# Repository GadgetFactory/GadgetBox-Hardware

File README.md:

GadgetBox tackles the biggest problems with current IoT devices – shield stacking, easily adding hardware, hardware compatibility, and an enclosure for your project. There are lots of IoT hardware options out there but none of them have thought the problem all the way through, so what we end up with is either a crazy tower of shields or peripherals soldered on with jumper wires. Not something we can proudly show our friends and family, let alone put into use in our homes.

GadgetBox starts with a case and builds from there – so the end result is an attractive, functional device with all of the electronics safely contained in the case.

Inside the GadgetBox case is a motherboard that provides all of the circuitry to charge and use a Lipo battery pack, provide higher current to your peripherals, and organizes all IO pins into the Universal eCog scheme. A motherboard for all of the most popular IoT devices is currently in the works – Arduino, Teensy, Pi Zero, ESP8266, etc.

eCogs are Universal peripherals that just snap into the motherboard and form the top of your enclosure. Only the hardware that is needed by the end user is exposed to the outside world, everything else is tucked inside the enclosure. Because the motherboards are designed using the Universal eCog scheme you can freely interchange your eCogs between motherboards. If you have an SD card eCog shouldn’t you be able to use that same eCog with the Arduino, Teensy, Pi Zero, and ESP8266? Of course you should, the Universal eCog scheme makes that possible.

Learn more at:
https://hackaday.io/project/12426-gadgetbox-no-more-shield-stacking-or-ugly-wires
http://GadgetBox.GadgetFactory.net

# GadgetBox-Hardware

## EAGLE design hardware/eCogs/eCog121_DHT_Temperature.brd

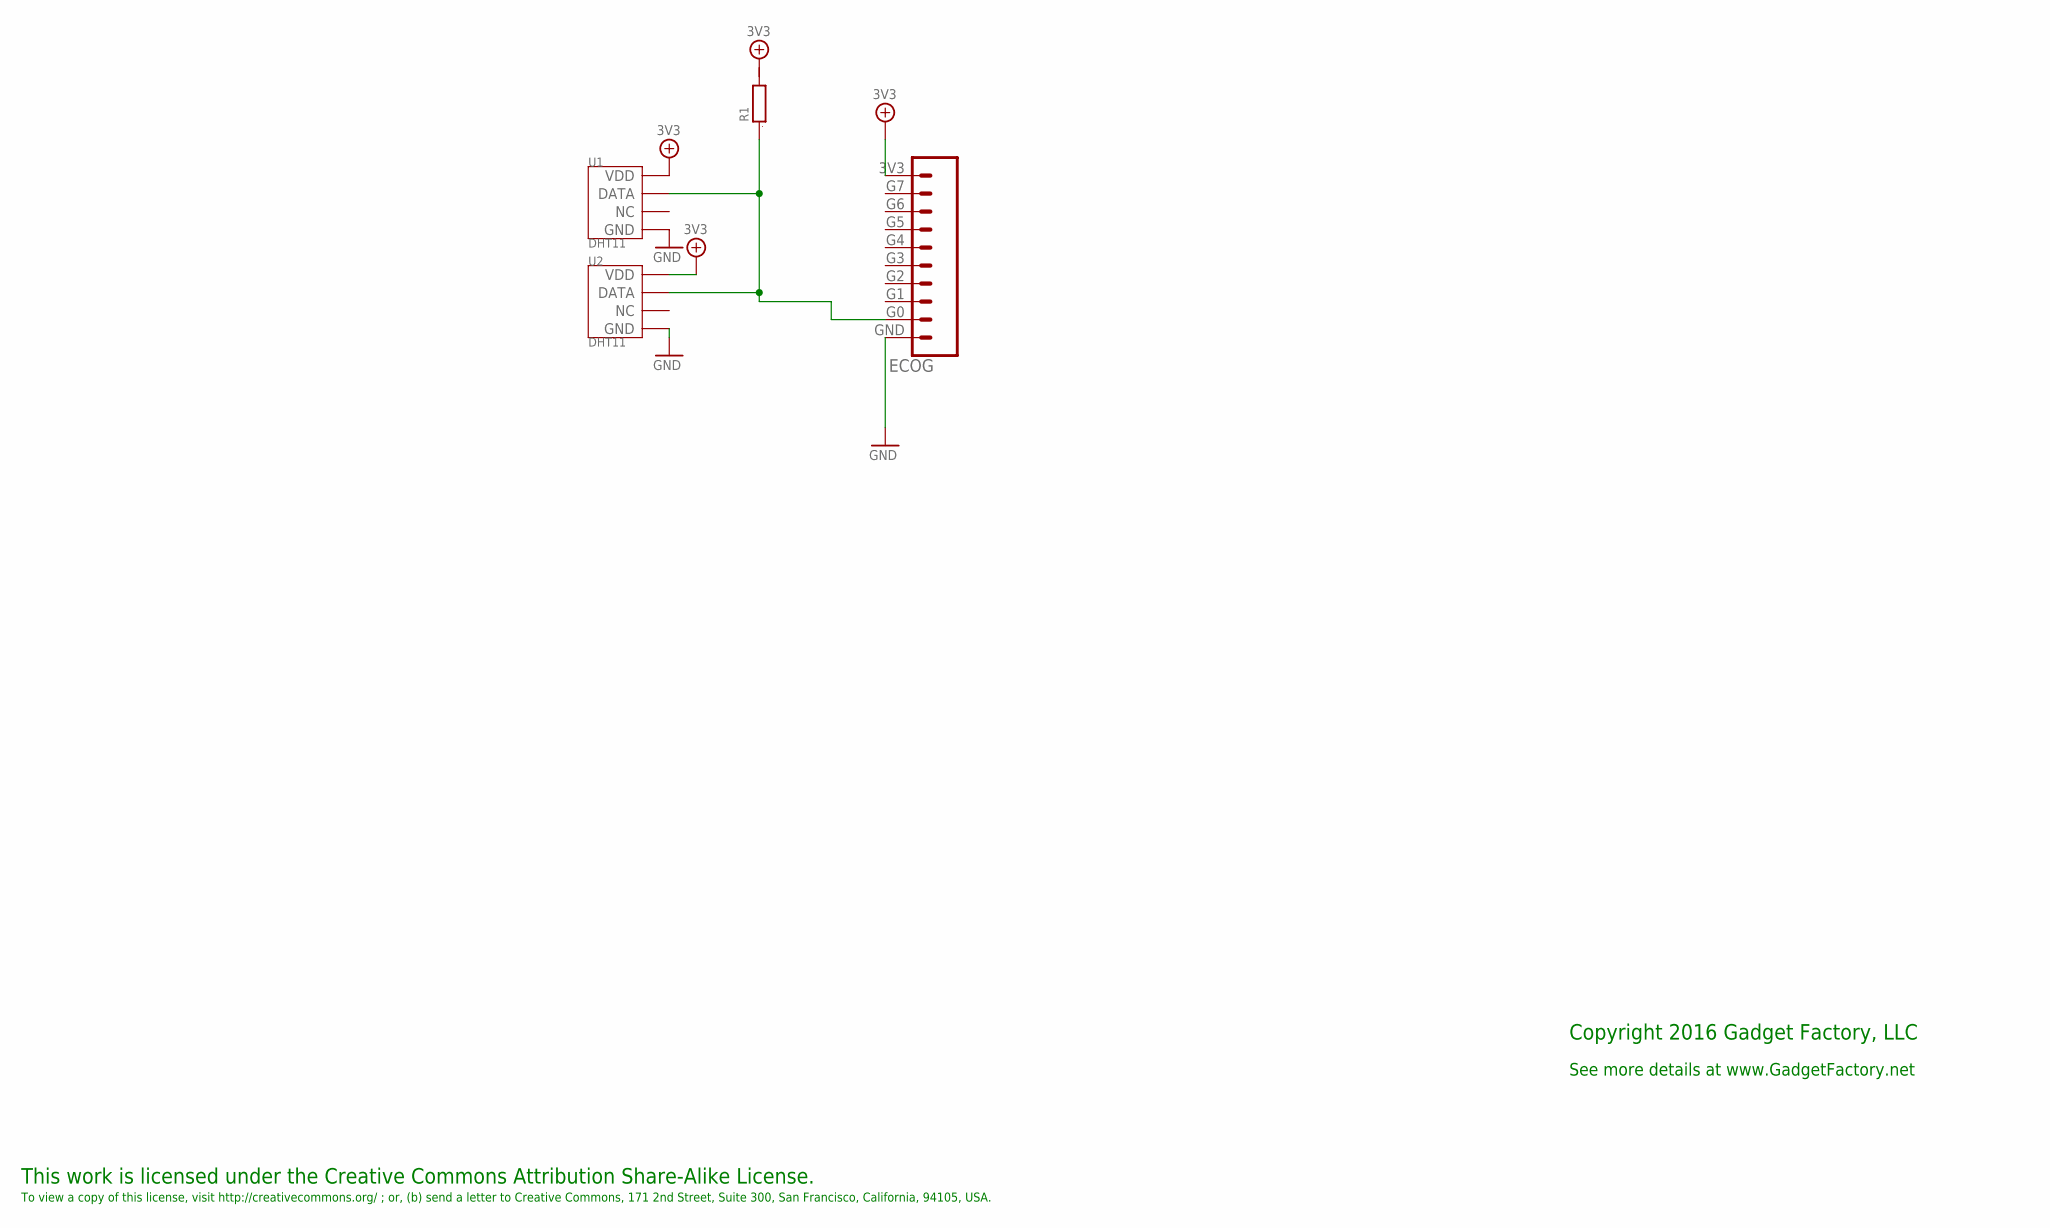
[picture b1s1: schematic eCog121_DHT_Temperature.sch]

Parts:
ECOG: ECOG_GENERAL_ROWTHROUGHOLE; ECOG_GENERAL_TH
R1: R0805; 0805
U1, U2: DHT11; SNR4-2.54-15.5X12.0X5.5MM

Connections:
3V3: ECOG.3V3, U1.1 (VDD)
GND: ECOG.GND, U1.4 (GND), U2.4 (GND)
unnamed: ECOG.G0, R1.1, U1.2 (DATA), U2.2 (DATA)
VDD: U2.1 (VDD)

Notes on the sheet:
This work is licensed under the Creative Commons Attribution Share-Alike License.
To view a copy of this license, visit http://creativecommons.org/ ; or, (b) send a letter to Creative Commons, 171 2nd Street, Suite 300, San Francisco, California, 94105, USA.
Copyright 2016 Gadget Factory, LLC
See more details at www.GadgetFactory.net

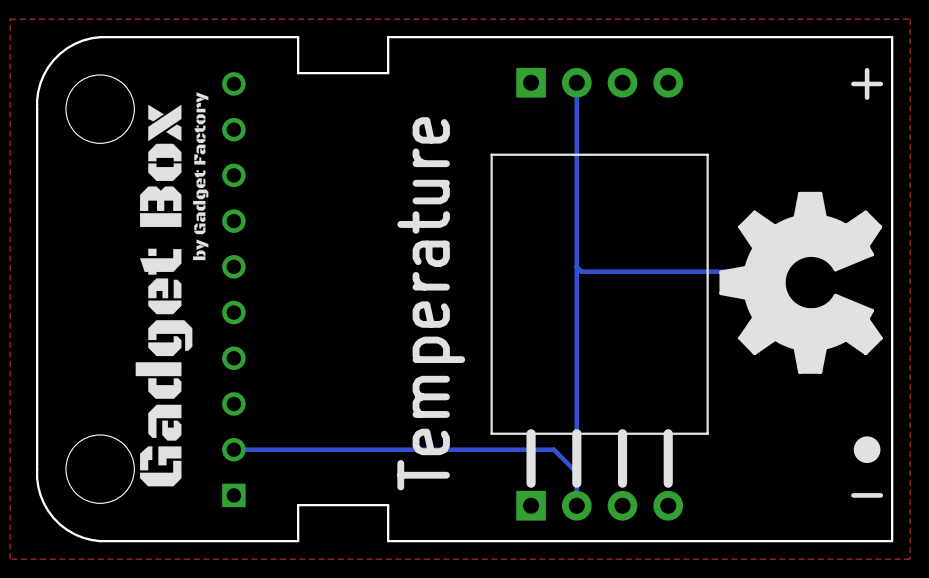
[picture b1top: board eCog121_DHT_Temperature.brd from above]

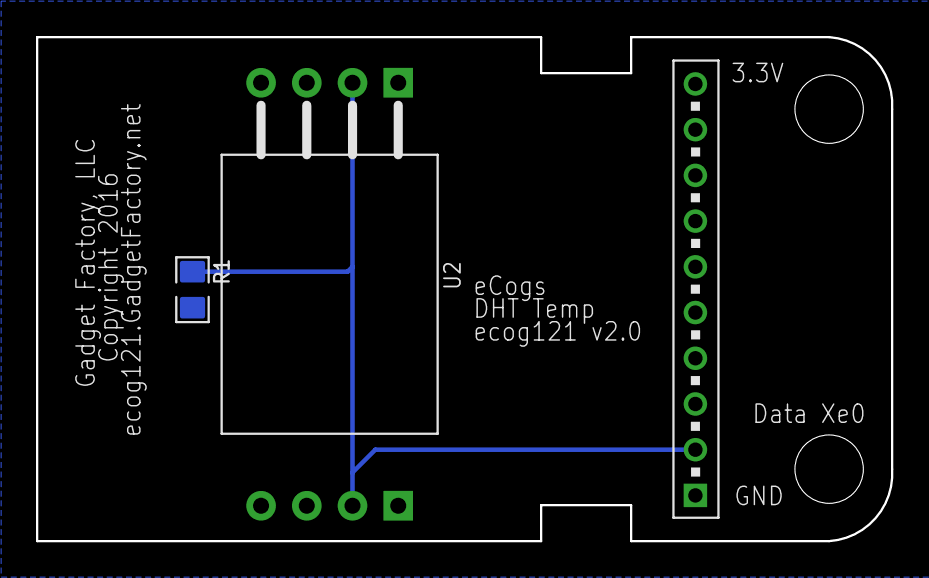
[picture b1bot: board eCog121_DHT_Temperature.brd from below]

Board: 2 copper layers, 47.5 x 28.0 mm, 7 parts (2 on the bottom side), 3 nets.

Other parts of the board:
U$1: GADGETBOX_SMALL
U$2: LEGEND_DIO
U$10: OSHW_FILLX350_NOTEXT

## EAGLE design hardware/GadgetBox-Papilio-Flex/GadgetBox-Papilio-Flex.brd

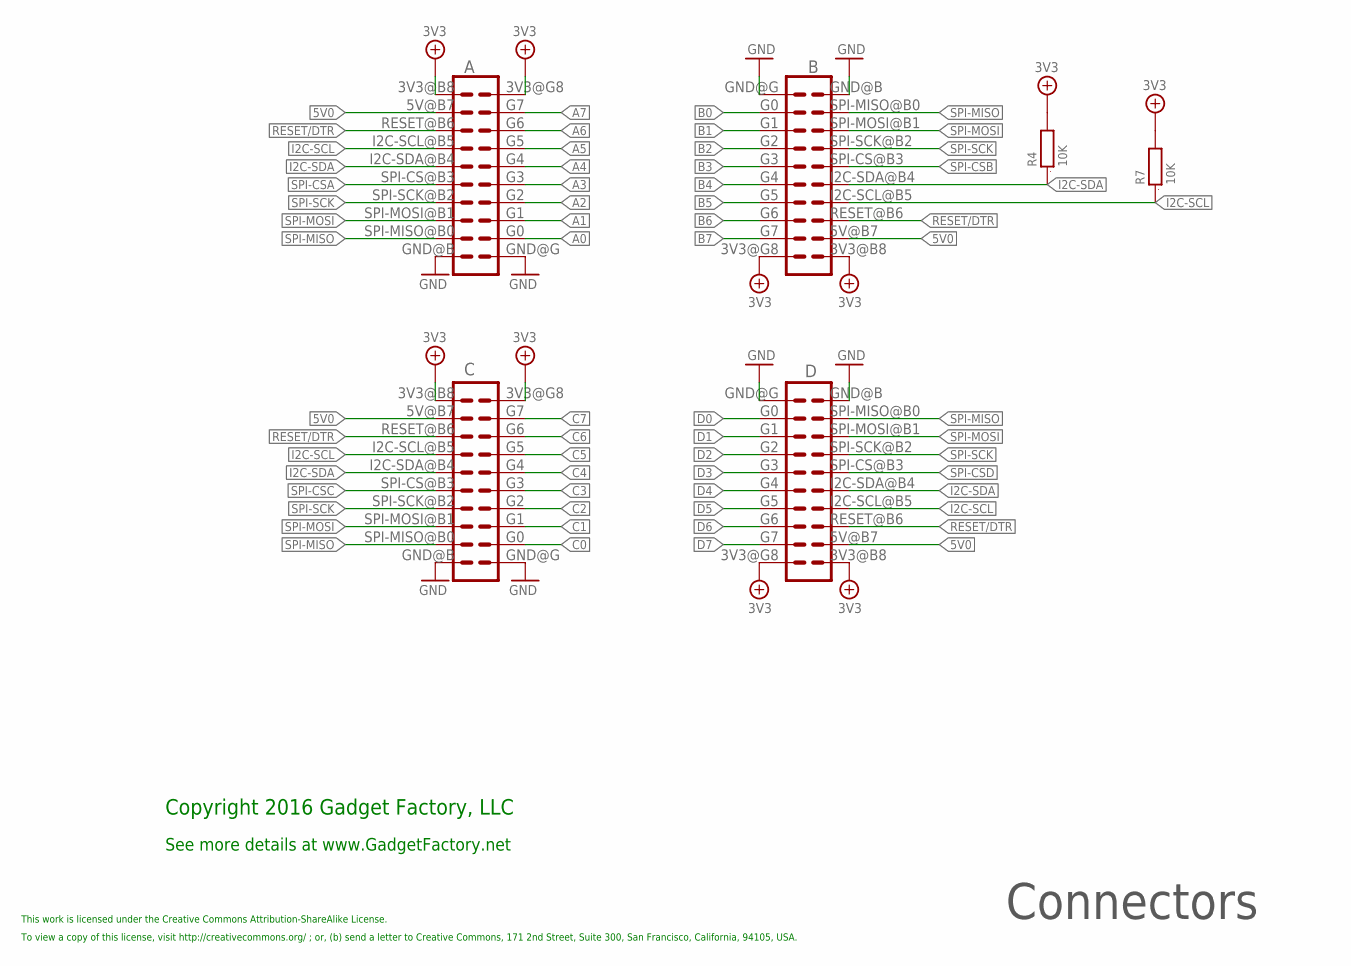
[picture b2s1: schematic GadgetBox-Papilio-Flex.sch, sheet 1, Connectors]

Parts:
A: ECOGECOG_SLOT_ALT1; ECOG_ALT1; PARTNO PPPC102LFBN-RC,SULLINS CONNECTOR SOLUTI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
B: ECOGECOG_SLOT_ALT1; ECOG_ALT1; PARTNO PPPC102LFBN-RC,SULLINS CONNECTOR SOLUTI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
C: ECOGECOG_SLOT_ALT1; ECOG_ALT1; PARTNO PPPC102LFBN-RC,SULLINS CONNECTOR SOLUTI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
D: ECOGECOG_SLOT_ALT1; ECOG_ALT1; PARTNO PPPC102LFBN-RC,SULLINS CONNECTOR SOLUTI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
R4, R7: 10K; 0603; PARTNO RC0603JR-0710KL,YAGEO (VA),dk,311-10KGR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

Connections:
3V3: A.3V3@B8 (3V3), A.3V3@G8 (3V3), B.3V3@B8 (3V3), B.3V3@G8 (3V3), C.3V3@B8 (3V3), C.3V3@G8 (3V3), D.3V3@B8 (3V3), D.3V3@G8 (3V3), R4.2, R7.2; also elsewhere on the board
5V0: A.5V@B7 (5V), B.5V@B7 (5V), C.5V@B7 (5V), D.5V@B7 (5V); also elsewhere on the board
A0: A.G0; also elsewhere on the board
A1: A.G1; also elsewhere on the board
A2: A.G2; also elsewhere on the board
A3: A.G3; also elsewhere on the board
A4: A.G4; also elsewhere on the board
A5: A.G5; also elsewhere on the board
A6: A.G6; also elsewhere on the board
A7: A.G7; also elsewhere on the board
B0: B.G0; also elsewhere on the board
B1: B.G1; also elsewhere on the board
B2: B.G2; also elsewhere on the board
B3: B.G3; also elsewhere on the board
B4: B.G4; also elsewhere on the board
B5: B.G5; also elsewhere on the board
B6: B.G6; also elsewhere on the board
B7: B.G7; also elsewhere on the board
C0: C.G0; also elsewhere on the board
C1: C.G1; also elsewhere on the board
C2: C.G2; also elsewhere on the board
C3: C.G3; also elsewhere on the board
C4: C.G4; also elsewhere on the board
C5: C.G5; also elsewhere on the board
C6: C.G6; also elsewhere on the board
C7: C.G7; also elsewhere on the board
D0: D.G0; also elsewhere on the board
D1: D.G1; also elsewhere on the board
D2: D.G2; also elsewhere on the board
D3: D.G3; also elsewhere on the board
D4: D.G4; also elsewhere on the board
D5: D.G5; also elsewhere on the board
D6: D.G6; also elsewhere on the board
D7: D.G7; also elsewhere on the board
GND: A.GND@B (GND), A.GND@G (GND), B.GND@B (GND), B.GND@G (GND), C.GND@B (GND), C.GND@G (GND), D.GND@B (GND), D.GND@G (GND); also elsewhere on the board
I2C-SCL: A.I2C-SCL@B5 (I2C-SCL), B.I2C-SCL@B5 (I2C-SCL), C.I2C-SCL@B5 (I2C-SCL), D.I2C-SCL@B5 (I2C-SCL), R7.1; also elsewhere on the board
I2C-SDA: A.I2C-SDA@B4 (I2C-SDA), B.I2C-SDA@B4 (I2C-SDA), C.I2C-SDA@B4 (I2C-SDA), D.I2C-SDA@B4 (I2C-SDA), R4.1; also elsewhere on the board
RESET/DTR: A.RESET@B6 (RESET), B.RESET@B6 (RESET), C.RESET@B6 (RESET), D.RESET@B6 (RESET); also elsewhere on the board
SPI-CSA: A.SPI-CS@B3 (SPI-CS); also elsewhere on the board
SPI-CSB: B.SPI-CS@B3 (SPI-CS); also elsewhere on the board
SPI-CSC: C.SPI-CS@B3 (SPI-CS); also elsewhere on the board
SPI-CSD: D.SPI-CS@B3 (SPI-CS); also elsewhere on the board
SPI-MISO: A.SPI-MISO@B0 (SPI-MISO), B.SPI-MISO@B0 (SPI-MISO), C.SPI-MISO@B0 (SPI-MISO), D.SPI-MISO@B0 (SPI-MISO); also elsewhere on the board
SPI-MOSI: A.SPI-MOSI@B1 (SPI-MOSI), B.SPI-MOSI@B1 (SPI-MOSI), C.SPI-MOSI@B1 (SPI-MOSI), D.SPI-MOSI@B1 (SPI-MOSI); also elsewhere on the board
SPI-SCK: A.SPI-SCK@B2 (SPI-SCK), B.SPI-SCK@B2 (SPI-SCK), C.SPI-SCK@B2 (SPI-SCK), D.SPI-SCK@B2 (SPI-SCK); also elsewhere on the board

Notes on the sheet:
Connectors
Copyright 2016 Gadget Factory, LLC
See more details at www.GadgetFactory.net
This work is licensed under the Creative Commons Attribution-ShareAlike License.
To view a copy of this license, visit http://creativecommons.org/ ; or, (b) send a letter to Creative Commons, 171 2nd Street, Suite 300, San Francisco, California, 94105, USA.

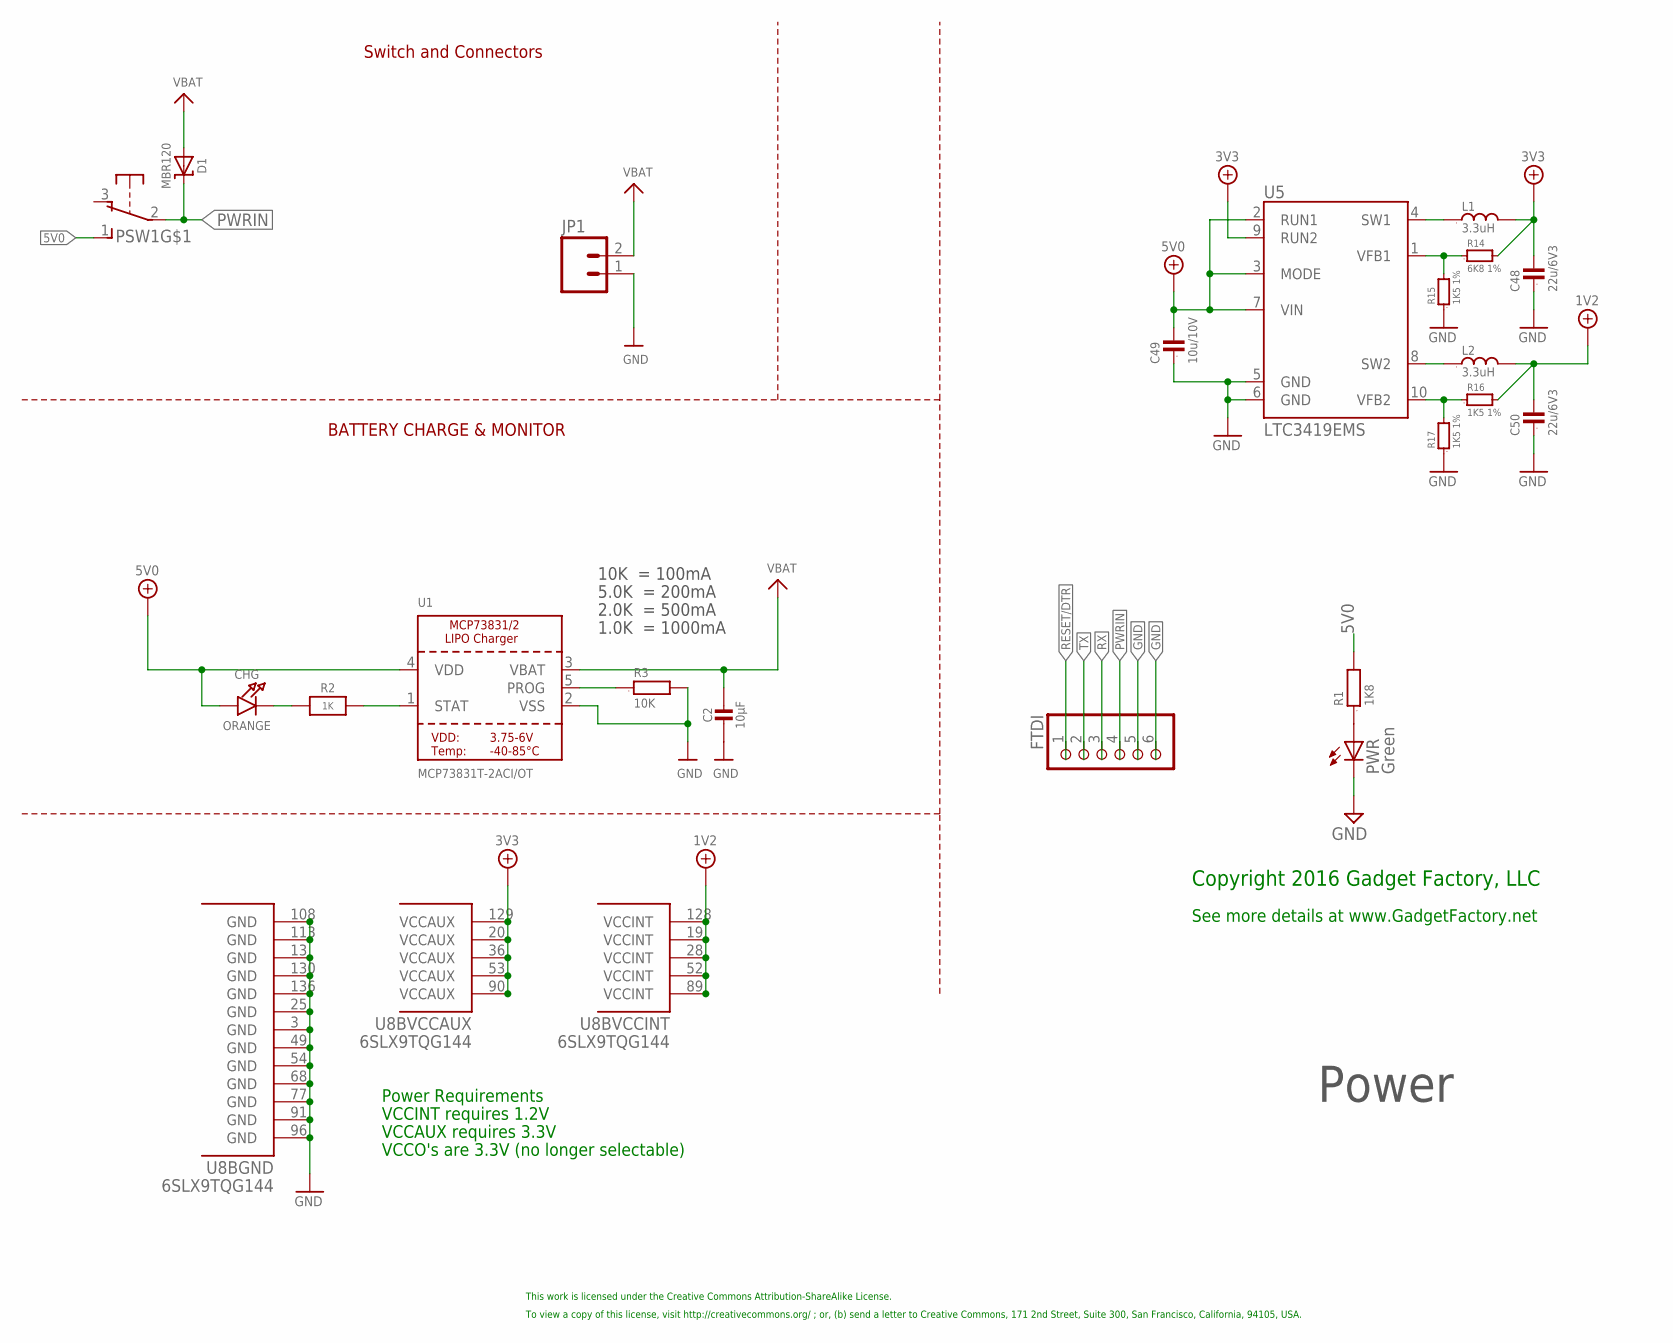
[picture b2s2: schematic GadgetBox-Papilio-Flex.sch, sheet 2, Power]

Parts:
C2: 10µF; 0805-NO; PARTNO CL21F106ZPFNNNE,Samsung,DK,1276-3012-1-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
C48, C50: 22u/6V3; 0805; PARTNO GRM21BR60J226ME39L,MURATA ELECTRONICS (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
C49: 10u/10V; 0805; PARTNO C2012Y5V1A106Z,TDK CORPORATION (VA),DK,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
CHG: ORANGE; CHIPLED_0805_NOOUTLINE; PARTNO LTST-C171EKT,LITE-ON INC (VA),DK,160-14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
D1: MBR120; SOD-123; PARTNO MBR120VLSFT3G,on semiconductor,dk,MBR12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
FTDI: PINHD-1X6; 1X06; PARTNO PPPC061LGBN-RC,SULLINS CONNECTOR SOLUTI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
JP1: M02JST-PTH-2; JST-2-PTH; PARTNO B2B-PH-SM4-TB(LF)(SN),JST SALES AMERICA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
L1, L2: 3.3uH; VLS3015; PARTNO VLS3015T-3R3M1R2,TDK CORPORATION (VA),D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
PSW1: OS102011MA1Q; PARTNO OS102011MA1QN1,C&K Components,dk,CKN955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
PWR: Green; CHIP-LED0805; PARTNO LTST-C170KGKT,LITE-ON INC (VA),DK,160-1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
R1: 1K8; 0805; PARTNO MCR10EZPJ182,ROHM SEMICONDUCTOR (PASSIV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
R2: 1K; 0603-NO; PARTNO RC0603JR-071KL,YAGEO (VA),dk,311-1.0KGR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
R3: 10K; 0603; PARTNO RC0603JR-0710KL,YAGEO (VA),dk,311-10KGR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
R14: 6K8 1%; 0603; PARTNO CRCW06036K80FKEA,VISHAY DALE (VA),DK,54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
R15, R16, R17: 1K5 1%; 0603; PARTNO CRCW06031K50FKEA,VISHAY DALE (VA),DK,54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
U1: MCP73831T-2ACI/OT; SOT23-5; PARTNO MCP73831T-2ACI/OT,MICROCHIP TECHNOLOGY 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
U5: LTC3419EMS; MSOP10; PARTNO LTC3419EMS#PBF,LINEAR TECHNOLOGY,DK,LTC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; DIGIKEY LTC3419EMS#PBF-ND
U8: 6SLX9TQG144; TQ144; PARTNO XC6SLX9-2TQG144C,XILINX INC,DK,122-1745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

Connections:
1V2: C50.2, L2.2, R16.2, U8.19 (VCCINT), U8.28 (VCCINT), U8.52 (VCCINT), U8.89 (VCCINT), U8.128 (VCCINT); also elsewhere on the board
3V3: C48.2, L1.2, R14.2, U5.9 (RUN2), U8.20 (VCCAUX), U8.36 (VCCAUX), U8.53 (VCCAUX), U8.90 (VCCAUX), U8.129 (VCCAUX); also elsewhere on the board
5V0: C49.2, CHG.A, PSW1.1 (S), R1.2, U1.4 (VDD), U5.2 (RUN1), U5.3 (MODE), U5.7 (VIN); also elsewhere on the board
FB_1V2: R16.1, R17.2, U5.10 (VFB2)
FB_3V3: R14.1, R15.2, U5.1 (VFB1)
GND: C2.2, C48.1, C49.1, C50.1, FTDI.5, FTDI.6, JP1.1, PWR.C, R3.2, R15.1, R17.1, U1.2 (VSS), U5.5 (GND), U5.6 (GND), U8.3 (GND), U8.13 (GND), U8.25 (GND), U8.49 (GND), U8.54 (GND), U8.68 (GND), U8.77 (GND), U8.91 (GND), U8.96 (GND), U8.108 (GND), U8.113 (GND), U8.130 (GND), U8.136 (GND); also elsewhere on the board
unnamed: PWR.A, R1.1
unnamed: CHG.C, R2.1
unnamed: R2.2, U1.1 (STAT)
unnamed: R3.1, U1.5 (PROG)
PWRIN: D1.C, FTDI.4, PSW1.2; also elsewhere on the board
RESET/DTR: FTDI.1; also elsewhere on the board
RX: FTDI.3; also elsewhere on the board
SW_1V2: L2.1, U5.8 (SW2)
SW_3V3: L1.1, U5.4 (SW1)
TX: FTDI.2; also elsewhere on the board
VBAT: C2.1, D1.A, JP1.2, U1.3 (VBAT)

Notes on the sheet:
Switch and Connectors
BATTERY CHARGE & MONITOR
10K = 100mA
5.0K = 200mA
2.0K = 500mA
1.0K = 1000mA
Power Requirements
VCCINT requires 1.2V
VCCAUX requires 3.3V
VCCO's are 3.3V (no longer selectable)
Power
Copyright 2016 Gadget Factory, LLC
See more details at www.GadgetFactory.net
This work is licensed under the Creative Commons Attribution-ShareAlike License.
To view a copy of this license, visit http://creativecommons.org/ ; or, (b) send a letter to Creative Commons, 171 2nd Street, Suite 300, San Francisco, California, 94105, USA.

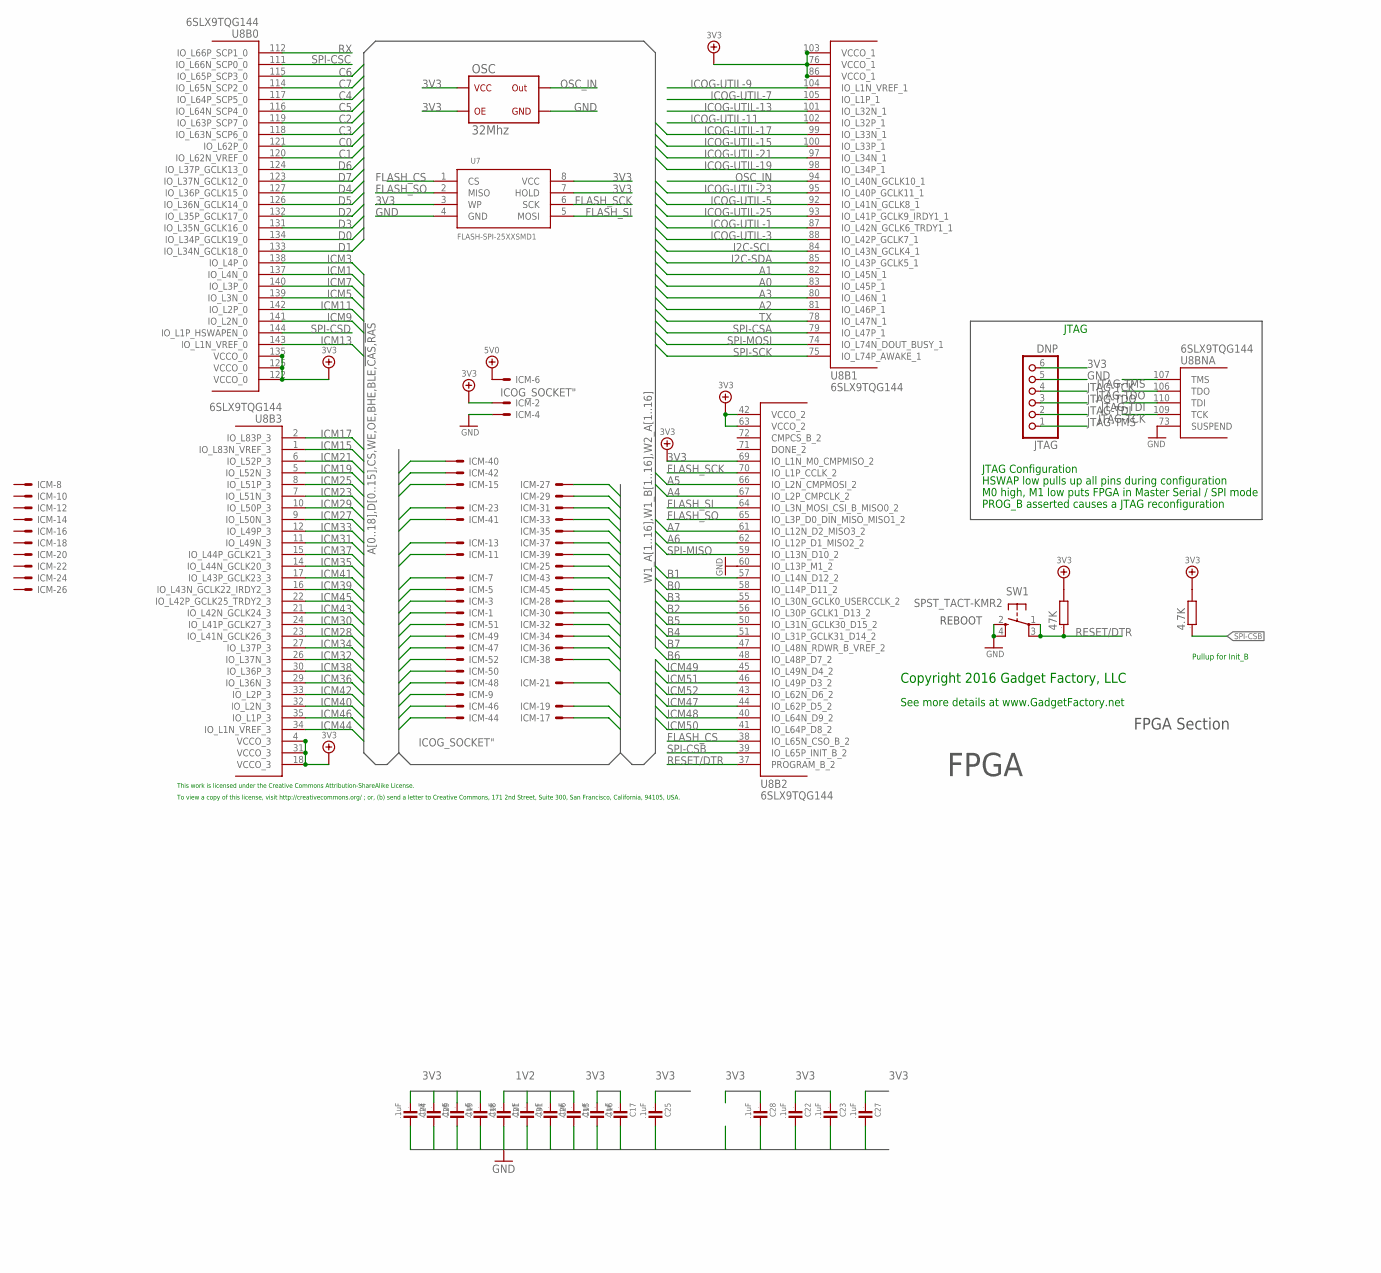
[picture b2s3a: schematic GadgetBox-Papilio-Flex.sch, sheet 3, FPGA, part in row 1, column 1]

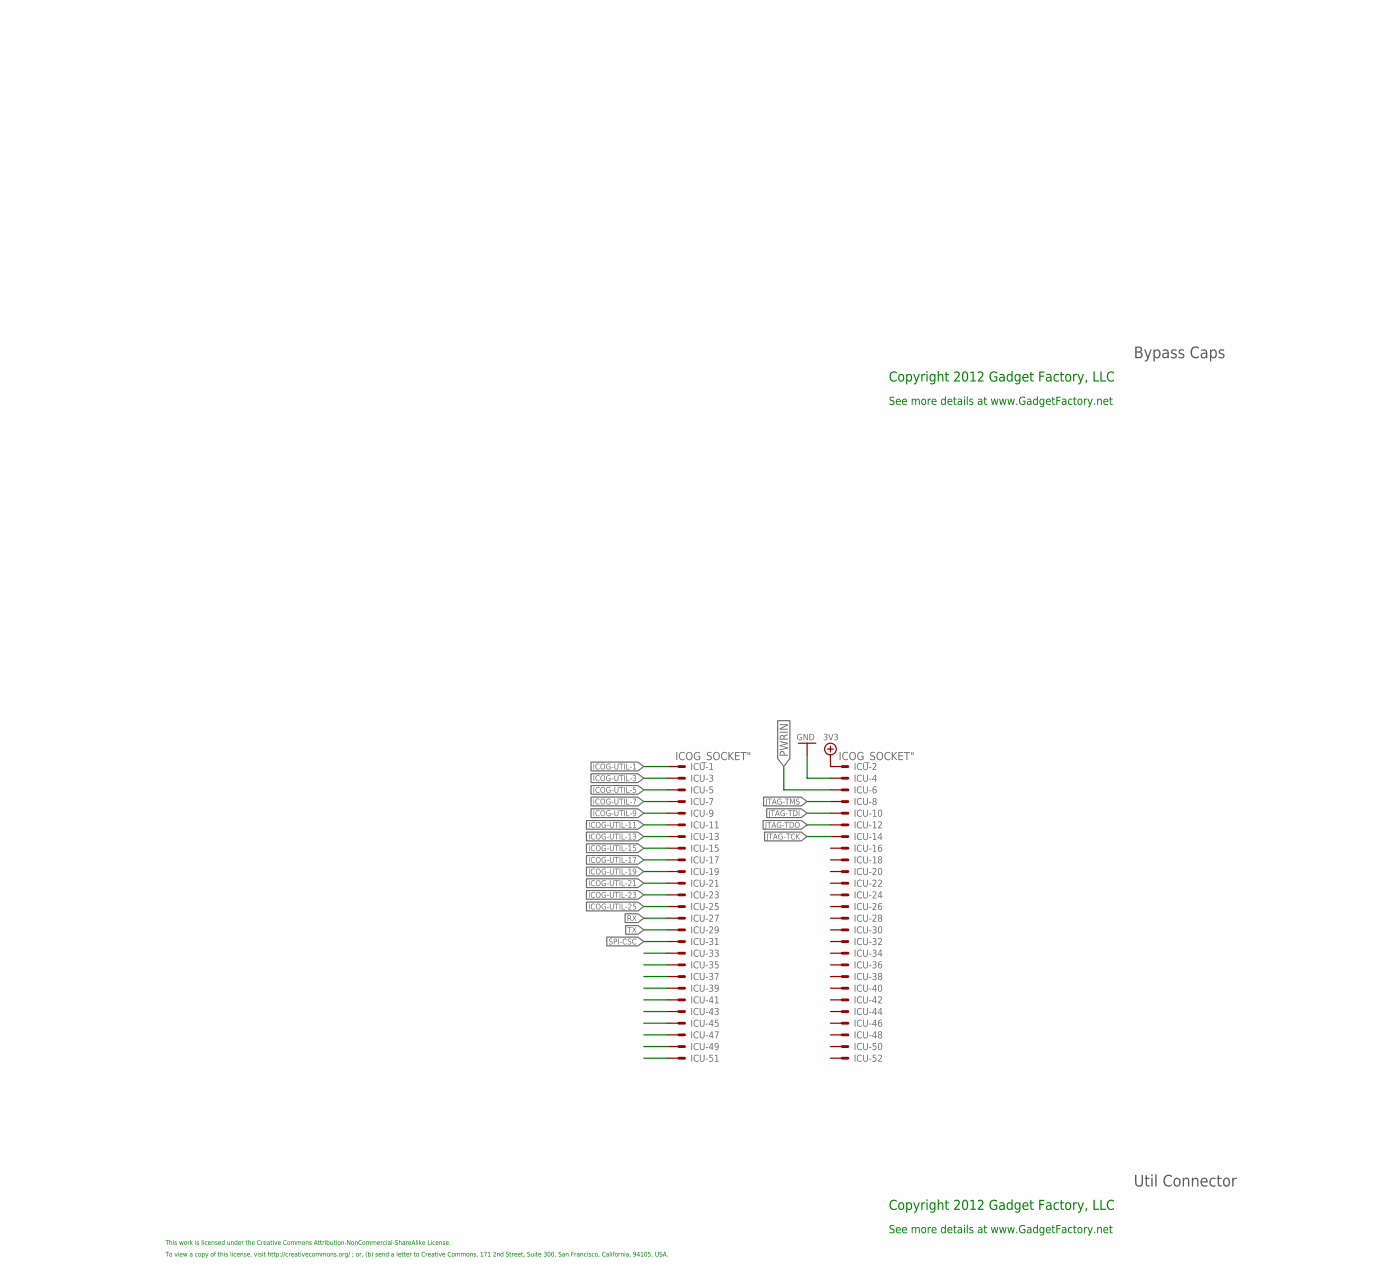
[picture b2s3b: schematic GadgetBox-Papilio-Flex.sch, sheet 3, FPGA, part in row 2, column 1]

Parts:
C15, C16, C17, C18, C19, C21, C22, C23, C24, C25, C26, C27, C28, C29, C31: .1uF; 0603; MPN 06033D105MAT2A
ICM: ICOG_SOCKET"; ICOG_STANDARD_STANDOFF; PARTNO 679105700,Molex,DK,WM7125CT-ND ,CONN ED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
ICU: ICOG_SOCKET"; ICOG_STANDARD_STANDOFF; PARTNO 679105700,Molex,DK,WM7125CT-ND ,CONN ED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
JTAG: DNP; 1X06
OSC: 32Mhz; OSC1; MPN LB2012T100KR
R6: 4.7K; 0603; PARTNO RC0603JR-0747KL,YAGEO (VA),dk,311-47KGR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
R33: 47K; 0603; PARTNO RC0603JR-0747KL,YAGEO (VA),dk,311-47KGR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
SW1: SPST_TACT-KMR2; KMR2; PARTNO KMR231NG LFS,C&K Components,dk,CKN10246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
U7: FLASH-SPI-25XXSMD1; SO08-EIAJ; PARTNO MX25L6445EM2I-10G,Macronix,DK,1092-1065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
U8: 6SLX9TQG144; TQ144; PARTNO XC6SLX9-2TQG144C,XILINX INC,DK,122-1745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

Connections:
1V2: C15.1, C21.1, C26.1, C31.1; also elsewhere on the board
3V3: C16.1, C17.1, C18.1, C19.1, C22.1, C23.1, C24.1, C25.1, C27.1, C28.1, C29.1, ICM.2, ICU.2, JTAG.6, OSC.1@1 (OE), OSC.4@4 (VCC), R6.2, R33.2, U7.3 (WP), U7.7 (HOLD), U7.8 (VCC), U8.4 (VCCO_3), U8.18 (VCCO_3), U8.31 (VCCO_3), U8.42 (VCCO_2), U8.63 (VCCO_2), U8.69 (IO_L1N_M0_CMPMISO_2), U8.76 (VCCO_1), U8.86 (VCCO_1), U8.103 (VCCO_1), U8.122 (VCCO_0), U8.125 (VCCO_0), U8.135 (VCCO_0); also elsewhere on the board
5V0: ICM.6; also elsewhere on the board
A0: U8.83 (IO_L45P_1); also elsewhere on the board
A1: U8.82 (IO_L45N_1); also elsewhere on the board
A2: U8.81 (IO_L46P_1); also elsewhere on the board
A3: U8.80 (IO_L46N_1); also elsewhere on the board
A4: U8.67 (IO_L2P_CMPCLK_2); also elsewhere on the board
A5: U8.66 (IO_L2N_CMPMOSI_2); also elsewhere on the board
A6: U8.62 (IO_L12P_D1_MISO2_2); also elsewhere on the board
A7: U8.61 (IO_L12N_D2_MISO3_2); also elsewhere on the board
B0: U8.58 (IO_L14P_D11_2); also elsewhere on the board
B1: U8.57 (IO_L14N_D12_2); also elsewhere on the board
B2: U8.56 (IO_L30P_GCLK1_D13_2); also elsewhere on the board
B3: U8.55 (IO_L30N_GCLK0_USERCCLK_2); also elsewhere on the board
B4: U8.51 (IO_L31P_GCLK31_D14_2); also elsewhere on the board
B5: U8.50 (IO_L31N_GCLK30_D15_2); also elsewhere on the board
B6: U8.48 (IO_L48P_D7_2); also elsewhere on the board
B7: U8.47 (IO_L48N_RDWR_B_VREF_2); also elsewhere on the board
C0: U8.121 (IO_L62P_0); also elsewhere on the board
C1: U8.120 (IO_L62N_VREF_0); also elsewhere on the board
C2: U8.119 (IO_L63P_SCP7_0); also elsewhere on the board
C3: U8.118 (IO_L63N_SCP6_0); also elsewhere on the board
C4: U8.117 (IO_L64P_SCP5_0); also elsewhere on the board
C5: U8.116 (IO_L64N_SCP4_0); also elsewhere on the board
C6: U8.115 (IO_L65P_SCP3_0); also elsewhere on the board
C7: U8.114 (IO_L65N_SCP2_0); also elsewhere on the board
D0: U8.134 (IO_L34P_GCLK19_0); also elsewhere on the board
D1: U8.133 (IO_L34N_GCLK18_0); also elsewhere on the board
D2: U8.132 (IO_L35P_GCLK17_0); also elsewhere on the board
D3: U8.131 (IO_L35N_GCLK16_0); also elsewhere on the board
D4: U8.127 (IO_L36P_GCLK15_0); also elsewhere on the board
D5: U8.126 (IO_L36N_GCLK14_0); also elsewhere on the board
D6: U8.124 (IO_L37P_GCLK13_0); also elsewhere on the board
D7: U8.123 (IO_L37N_GCLK12_0); also elsewhere on the board
FLASH_CS: U7.1 (CS), U8.38 (IO_L65N_CSO_B_2)
FLASH_SCK: U7.6 (SCK), U8.70 (IO_L1P_CCLK_2)
FLASH_SI: U7.5 (MOSI), U8.64 (IO_L3N_MOSI_CSI_B_MISO0_2)
FLASH_SO: U7.2 (MISO), U8.65 (IO_L3P_D0_DIN_MISO_MISO1_2)
GND: C15.2, C16.2, C17.2, C18.2, C19.2, C21.2, C22.2, C23.2, C24.2, C25.2, C26.2, C27.2, C28.2, C29.2, C31.2, ICM.4, ICU.4, JTAG.5, OSC.2@2 (GND), SW1.2 (S), SW1.4 (S1), U7.4 (GND), U8.60 (IO_L13P_M1_2), U8.73 (SUSPEND); also elsewhere on the board
I2C-SCL: U8.84 (IO_L43N_GCLK4_1); also elsewhere on the board
I2C-SDA: U8.85 (IO_L43P_GCLK5_1); also elsewhere on the board
ICM1: ICM.1, U8.137 (IO_L4N_0)
ICM3: ICM.3, U8.138 (IO_L4P_0)
ICM5: ICM.5, U8.139 (IO_L3N_0)
ICM7: ICM.7, U8.140 (IO_L3P_0)
ICM9: ICM.9, U8.141 (IO_L2N_0)
ICM11: ICM.11, U8.142 (IO_L2P_0)
ICM13: ICM.13, U8.143 (IO_L1N_VREF_0)
ICM15: ICM.15, U8.1 (IO_L83N_VREF_3)
ICM17: ICM.17, U8.2 (IO_L83P_3)
ICM19: ICM.19, U8.5 (IO_L52N_3)
ICM21: ICM.21, U8.6 (IO_L52P_3)
ICM23: ICM.23, U8.7 (IO_L51N_3)
ICM25: ICM.25, U8.8 (IO_L51P_3)
ICM27: ICM.27, U8.9 (IO_L50N_3)
ICM28: ICM.28, U8.23 (IO_L41N_GCLK26_3)
ICM29: ICM.29, U8.10 (IO_L50P_3)
ICM30: ICM.30, U8.24 (IO_L41P_GCLK27_3)
ICM31: ICM.31, U8.11 (IO_L49N_3)
ICM32: ICM.32, U8.26 (IO_L37N_3)
ICM33: ICM.33, U8.12 (IO_L49P_3)
ICM34: ICM.34, U8.27 (IO_L37P_3)
ICM35: ICM.35, U8.14 (IO_L44N_GCLK20_3)
ICM36: ICM.36, U8.29 (IO_L36N_3)
ICM37: ICM.37, U8.15 (IO_L44P_GCLK21_3)
ICM38: ICM.38, U8.30 (IO_L36P_3)
ICM39: ICM.39, U8.16 (IO_L43N_GCLK22_IRDY2_3)
ICM40: ICM.40, U8.32 (IO_L2N_3)
ICM41: ICM.41, U8.17 (IO_L43P_GCLK23_3)
ICM42: ICM.42, U8.33 (IO_L2P_3)
ICM43: ICM.43, U8.21 (IO_L42N_GCLK24_3)
ICM44: ICM.44, U8.34 (IO_L1N_VREF_3)
ICM45: ICM.45, U8.22 (IO_L42P_GCLK25_TRDY2_3)
ICM46: ICM.46, U8.35 (IO_L1P_3)
ICM47: ICM.47, U8.44 (IO_L62P_D5_2)
ICM48: ICM.48, U8.40 (IO_L64N_D9_2)
ICM49: ICM.49, U8.45 (IO_L49N_D4_2)
ICM50: ICM.50, U8.41 (IO_L64P_D8_2)
ICM51: ICM.51, U8.46 (IO_L49P_D3_2)
ICM52: ICM.52, U8.43 (IO_L62N_D6_2)
ICOG-UTIL-1: ICU.1, U8.87 (IO_L42N_GCLK6_TRDY1_1)
ICOG-UTIL-3: ICU.3, U8.88 (IO_L42P_GCLK7_1)
ICOG-UTIL-5: ICU.5, U8.92 (IO_L41N_GCLK8_1)
ICOG-UTIL-7: ICU.7, U8.105 (IO_L1P_1)
ICOG-UTIL-9: ICU.9, U8.104 (IO_L1N_VREF_1)
ICOG-UTIL-11: ICU.11, U8.102 (IO_L32P_1)
ICOG-UTIL-13: ICU.13, U8.101 (IO_L32N_1)
ICOG-UTIL-15: ICU.15, U8.100 (IO_L33P_1)
ICOG-UTIL-17: ICU.17, U8.99 (IO_L33N_1)
ICOG-UTIL-19: ICU.19, U8.98 (IO_L34P_1)
ICOG-UTIL-21: ICU.21, U8.97 (IO_L34N_1)
ICOG-UTIL-23: ICU.23, U8.95 (IO_L40P_GCLK11_1)
ICOG-UTIL-25: ICU.25, U8.93 (IO_L41P_GCLK9_IRDY1_1)
JTAG-TCK: ICU.14, JTAG.4, U8.109 (TCK)
JTAG-TDI: ICU.10, JTAG.2, U8.110 (TDI)
JTAG-TDO: ICU.12, JTAG.3, U8.106 (TDO)
JTAG-TMS: ICU.8, JTAG.1, U8.107 (TMS)
OSC_IN: OSC.3@3 (OUT), U8.94 (IO_L40N_GCLK10_1)
PWRIN: ICU.6; also elsewhere on the board
RESET/DTR: R33.1, SW1.1, SW1.3 (P1), U8.37 (PROGRAM_B_2); also elsewhere on the board
RX: ICU.27, U8.112 (IO_L66P_SCP1_0); also elsewhere on the board
SPI-CSA: U8.79 (IO_L47P_1); also elsewhere on the board
SPI-CSB: R6.1, U8.39 (IO_L65P_INIT_B_2); also elsewhere on the board
SPI-CSC: ICU.31, U8.111 (IO_L66N_SCP0_0); also elsewhere on the board
SPI-CSD: U8.144 (IO_L1P_HSWAPEN_0); also elsewhere on the board
SPI-MISO: U8.59 (IO_L13N_D10_2); also elsewhere on the board
SPI-MOSI: U8.74 (IO_L74N_DOUT_BUSY_1); also elsewhere on the board
SPI-SCK: U8.75 (IO_L74P_AWAKE_1); also elsewhere on the board
TX: ICU.29, U8.78 (IO_L47N_1); also elsewhere on the board

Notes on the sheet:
JTAG Configuration
HSWAP low pulls up all pins during configuration
M0 high, M1 low puts FPGA in Master Serial / SPI mode
PROG_B asserted causes a JTAG reconfiguration
JTAG
Copyright 2016 Gadget Factory, LLC
See more details at www.GadgetFactory.net
This work is licensed under the Creative Commons Attribution-NonCommercial-ShareAlike License.
To view a copy of this license, visit http://creativecommons.org/ ; or, (b) send a letter to Creative Commons, 171 2nd Street, Suite 300, San Francisco, California, 94105, USA.
Bypass Caps
Util Connector
FPGA Section
REBOOT
Copyright 2012 Gadget Factory, LLC
This work is licensed under the Creative Commons Attribution-ShareAlike License.
Pullup for Init_B
FPGA

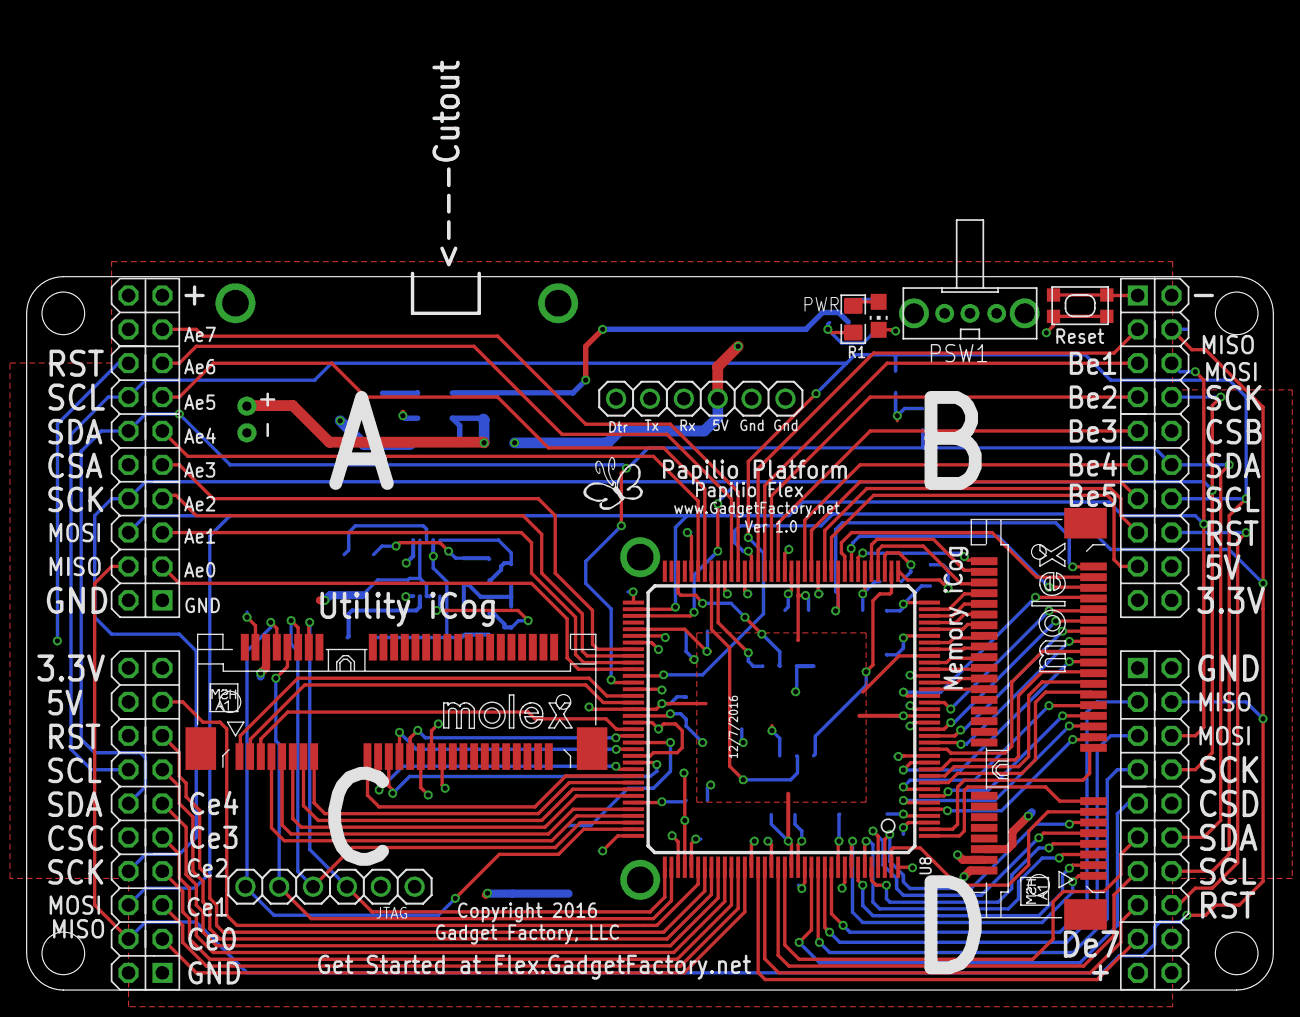
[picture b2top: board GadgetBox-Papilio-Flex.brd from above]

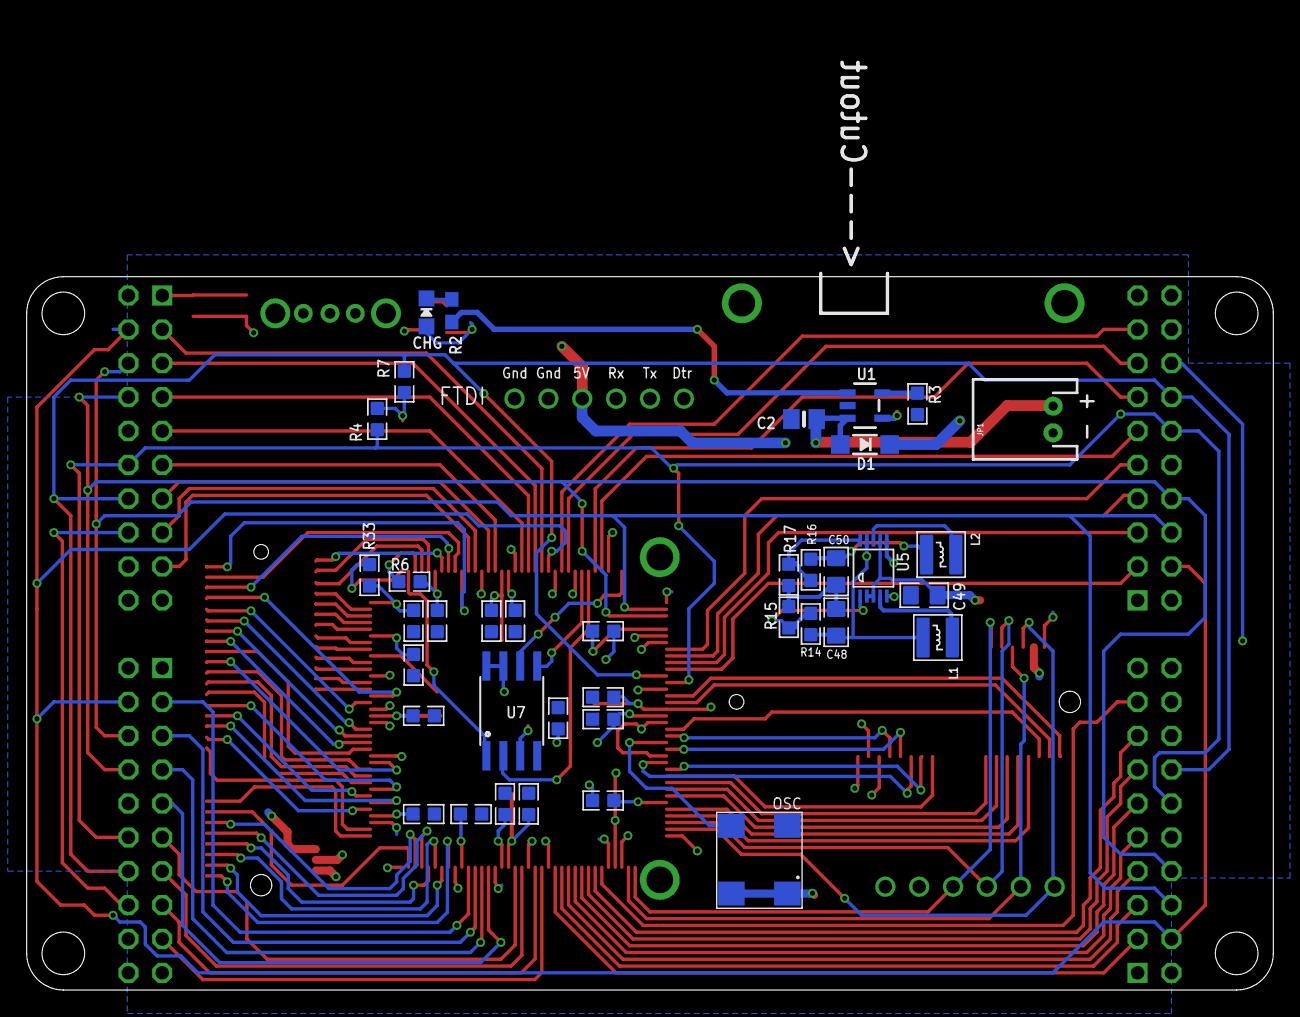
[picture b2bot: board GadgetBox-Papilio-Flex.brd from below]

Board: 4 copper layers, 93.2 x 72.0 mm, 53 parts (38 on the bottom side), 119 nets.

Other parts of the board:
$$U$1: ECOG93P53P5
U$14: GADGETFACTORY_LOGO

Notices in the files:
parts and their libraries:
microbuilder: This work is placed in the public domain, and may be freely used for commercial and non-commercial work with the following conditions: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
SparkFun: Licensing: CC v3.0 Share-Alike You are welcome to use this library for commercial purposes.
